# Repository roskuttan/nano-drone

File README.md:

# Nano drone

> [!WARNING]
> **AI-generated and not yet verified in hardware.** This design was produced by Claude (Anthropic's AI) working with
> me. That covers schematic, layout, routing, simulations, fab files and enclosure. No board has been built, powered
> or flown yet. It passes DRC and the simulations in this repo, but simulations are not a substitute for testing.
> Review it yourself before ordering, and use it at your own risk.

> [!NOTE]
> **The controller is not made yet.** This repo has only the drone hardware. Nothing exists yet for the side that
> flies it: no handheld transmitter setup, no phone app, no bridge. The firmware (Rust) for the flight controller and
> the ESCs isn't written either.

A brushless micro quad whose flight board is also its frame: a 36 × 36 mm, 6-layer board carrying an STM32G431
flight controller, four STM32G071 + DRV8311H ESCs, an SX1280 2.4 GHz ELRS radio and an LSM6DSV16X IMU, flying four
0702 motors. Everything is generated by code: schematic, placement, routing, fab outputs and simulations.

<p align="center">
  
</p>

<p align="center"><b>▶ <a href="media/nanodrone_video.mp4?raw=true">Watch the full video in HD</a></b> (40 s, opens in the browser's player)</p>

## PCB (rev C, fully routed: 110/110 nets, DRC 0 errors)

| Top | Bottom |
|---|---|
|  |  |

## Enclosure

| Assembled | Top view |
|---|---|
|  |  |

## Where things are

- [`hw/README.md`](hw/README.md): the generation pipeline, step by step, and how the rev C board was routed.
- [`hw/docs/ARCHITECTURE.md`](hw/docs/ARCHITECTURE.md): system architecture, pin maps, PCB and EMC design.
- [`hw/docs/FIRMWARE_REQUIREMENTS.md`](hw/docs/FIRMWARE_REQUIREMENTS.md): what the (Rust) firmware must do.
- [`hw/sim_post/POST_LAYOUT_REPORT.md`](hw/sim_post/POST_LAYOUT_REPORT.md): post-layout simulations on the routed copper.
- [`hw/output/fab/`](hw/output/fab/): JLCPCB package (Gerbers, BOM, CPL, order notes, STEP).
- [`hw/docs/ENCLOSURE.md`](hw/docs/ENCLOSURE.md): 3D-printed enclosure.

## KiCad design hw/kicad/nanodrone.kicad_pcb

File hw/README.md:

# Nano drone hardware

The flight board is generated by code: schematic, placement, routing, planes, fab outputs and simulations all come
from the Python scripts here. Run them with KiCad 10's bundled Python
(`C:\Users\angel\AppData\Local\Programs\KiCad\10.0\bin\python.exe`).

| Step | Command (from `hw/`) | Output |
|---|---|---|
| 1. Schematic + ERC | `python design/nanodrone_sch.py`, then `kicad-cli sch erc kicad/nanodrone.kicad_sch` | `kicad/*.kicad_sch` |
| 2. Placement + outline | `python design/nanodrone_pcb.py` | `kicad/nanodrone.kicad_pcb` |
| 3. Rules, stackup, critical copper | `python design/nanodrone_route.py prep` | RF feed, driver power, fan-out, escape stubs, planes |
| 4. Routing | `python design/nanodrone_route.py grid` | grid maze router with rip-up and reroute (`tools/gridroute.py`) |
| 4b. Routing, hybrid (alternative to 4) | `python design/nanodrone_route.py route`, then `... repair` | Freerouting for the bulk (prep copper stays locked). `repair` runs DRC and lifts the autorouted copper into the grid router as rip-able routes. It then re-routes incomplete nets and every net in a violation (Freerouting cannot see the `.kicad_dru` EMC rules) with full rules, and prunes dangling copper |
| 5. Finish | `python design/nanodrone_route.py finish` | widen power/phase, pours, stitching/thermal/return vias, DRC |
| 6. Fab package | `python design/nanodrone_fab.py` | `output/fab/`: Gerbers + drill zip, JLC BOM/CPL, order notes, renders, STEP |
| 7. Post-layout simulations | `python sim_post/run_post.py`, then `python sim_post/report.py` | `sim_post/POST_LAYOUT_REPORT.md` |
| Pre-layout simulations | `python sim/run_all.py` | `sim/SIMULATION_REPORT.md` |
| 8. Enclosure | `python tools/board_ref.py <placed or routed board>`, then run the Fusion script `mech/fusion/nanodrone_enclosure` | `output/mech/enclosure/`: STL/STEP for the 3D-printed shells, fit checks, renders (`docs/ENCLOSURE.md`) |

All stages work on `kicad/nanodrone.kicad_pcb`. To work on a copy, set `NANODRONE_PCB` to another board path. For
KiCad's DRC to pick up the design rules, copy `kicad/nanodrone.kicad_pro` and `.kicad_dru` next to that board under
the same base name. `patch_project(pro, dru)` in `design/nanodrone_route.py` writes them for a variant's rules.

The finish stage (step 5) now also removes unused driver escape stubs (`trim_stubs`). It widens only the fixed
motor-current legs; the sense branches stay narrow. Its return-path stitching serves first the signal vias that move
between the L2 and L5 return planes.

### How the rev C board was routed

No single command reproduces the routed board. Steps 1-4 got to 102/110 nets. The rest came from a chain of
seeded repair runs on copies of the board (`NANODRONE_PCB=kicad/nanodrone_<x>.kicad_pcb`). Each run re-routes
only the nets it is told to rip:

1. `legs`: the 12 motor-current legs become fixed copper.
2. `eco_nfault`: removes the four nFAULT pull-ups (rev C, `NANODRONE_NFAULT_PU=0` in the schematic).
3. `repair`, with these settings:
   - 0.10 mm sense branches (`NANODRONE_PHASE_W`), 0.20 mm phase-to-analog spacing;
   - L4 open to digital, rail and analog nets;
   - negotiated congestion. This reached 108/110 (board N20).
4. Local finishing runs on the 0.0125 mm grid (`NANODRONE_GRID_RES`). Each one rips a few named nets
   (`NANODRONE_RIP`), routes them in a set order (`NANODRONE_ORDER`) and keeps the nets it must not touch
   (`NANODRONE_KEEP`). Weighted A* (`NANODRONE_ASTAR_W=1.2`) keeps them fast.
5. `eco_m4col`: moves motor 4's BEMF divider column 0.2 mm east (`M4_COL_X` in `design/nanodrone_pcb.py`), so
   ESC4's SWD pins get via sites.
6. Local finishing with phase sense branches allowed on L4. In order:
   - the rest of the SWD clock;
   - motor 1's phase A/B sense lines, which had blocked ESC1's SWCLK pin;
   - motor 4 phase A, after moving ESC4_SWDIO off its via site;
   - M4_DSHOT and M4_INLA, whose vias the column shift had come too close to.

   The result is `kicad/attempts/nanodrone_r1.kicad_pcb`: 110/110 nets. All intermediate boards are kept in
   `kicad/attempts/`.
7. The finish stage then found a floating B-pour island under U24. It held J2's antenna GND pad and the GND pads of
   motor 4's BEMF B/C dividers, so those dividers had no ground. No via fitted inside the island.
   - A GND via went in at (-3.76, -6.24), the one spot inside the island blocked only by a single net (M4_nSLEEP).
   - M4_nSLEEP was re-routed off L4. Analog and control nets re-routed through L4 there could split the VBAT plane
     feeding motor 4's driver.
   - Result: `kicad/nanodrone_z2.kicad_pcb`. DRC shows 0 violations and 0 unconnected items.

The finish stage now runs `stitch_islands`. It gives any GND pour island without a via its own via, or reports it.

Router lessons from that work (`tools/gridroute.py`):
- **Own copper:** counts as free only after eroding it by half a track plus the grid margin. Otherwise connections
  creep into a neighbour's clearance; this caused a real short.
- **Hard cells:** these and the board edge keep half a track. No-net pads keep 0.15 mm plus their mask opening.
- **Grid size:** 0.0125 mm wins about 10-20 % of channel capacity over 0.025 mm.
- **Multi-pin nets:** retry from another pin when the first one is boxed in, and defer clusters that fail.
- **KiCad rules:** the last matching custom rule wins, so the specific phase-to-analog rule comes last in
  `.kicad_dru`. `kicad-cli` needs `--all-track-errors` to report every error on a track.

Documents:
- `docs/ARCHITECTURE.md`: system architecture, pin maps, PCB, EMC and firmware notes.
- `docs/FIRMWARE_REQUIREMENTS.md`: what the Rust firmware must do because of the hardware.
- `docs/COST_ESTIMATE.md`: batch and per-drone cost.
- `docs/ENCLOSURE.md`: 3D-printed enclosure: design, mass and TWR, fit checks, printing and assembly.

Tools:
- `tools/kisch.py`: schematic-as-code.
- `tools/kifp.py`: custom footprints.
- `tools/kipcb.py`: placement helpers.
- `tools/gridroute.py`: router.
- `tools/render.py` and `tools/zoom.py`: PNG views.
- `tools/board_ref.py`: mechanical reference of the board (outline, holes, part boxes, motors) for the enclosure.
- `mech/enclosure_calcs.py`: hand calculations for the enclosure (duct sections, ring mode, struts, mass/TWR).

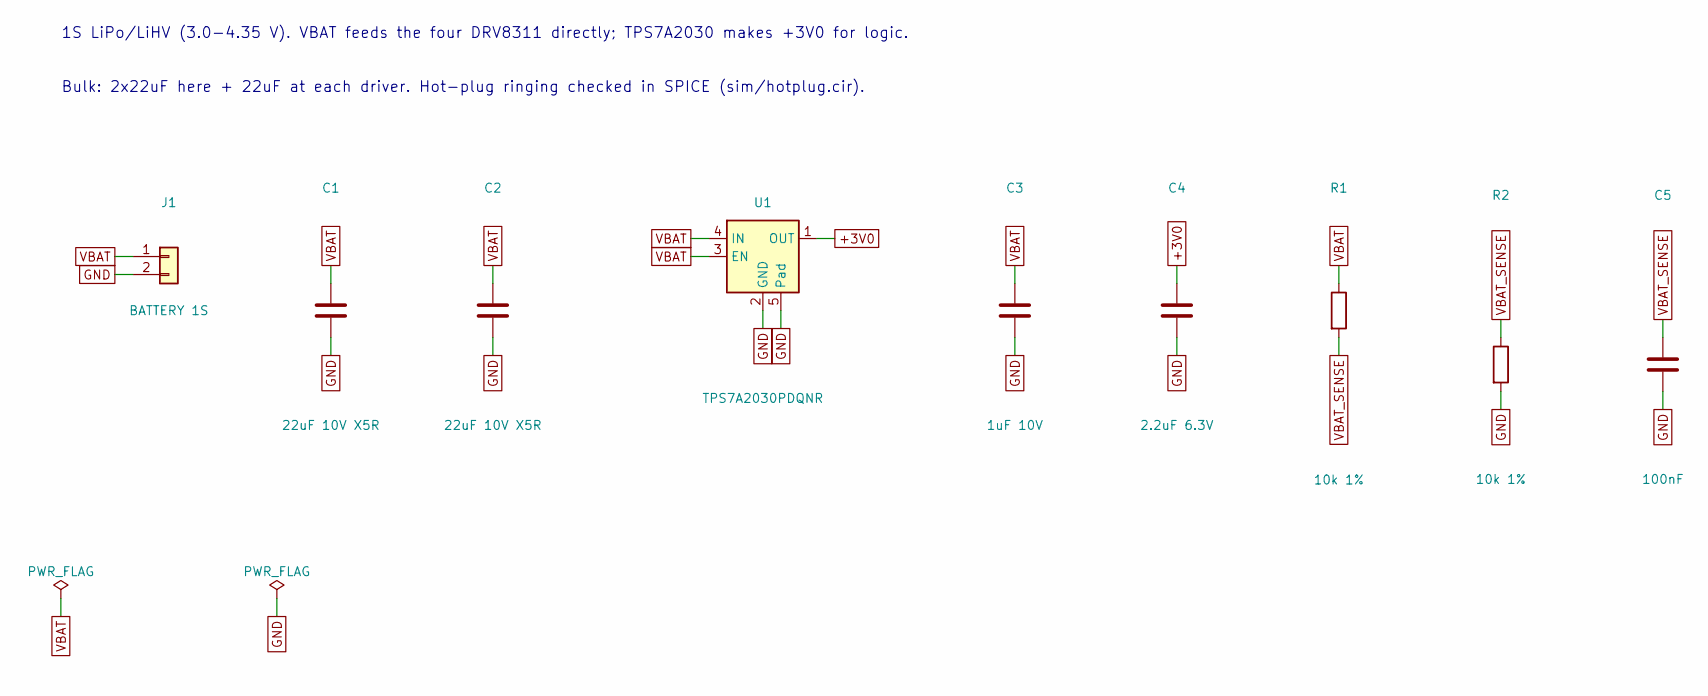
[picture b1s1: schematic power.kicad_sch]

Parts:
C1, C2: 22uF 10V X5R; C_0603_1608Metric
C3: 1uF 10V; C_0402_1005Metric
C4: 2.2uF 6.3V; C_0402_1005Metric
C5: 100nF; C_0201_0603Metric
J1: BATTERY 1S; BatteryPads_PTH
R1, R2: 10k 1%; R_0201_0603Metric
U1: TPS7A2030PDQNR; Texas_X2SON-4_1x1mm_P0.65mm; MPN TPS7A2030PDQNR

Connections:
+3V0: C4.1, U1.1 (OUT); also elsewhere on the board
GND: C1.2, C2.2, C3.2, C4.2, C5.2, J1.2, R2.2, U1.2 (GND), U1.5 (Pad); also elsewhere on the board
VBAT: C1.1, C2.1, C3.1, J1.1, R1.1, U1.3 (EN), U1.4 (IN); also elsewhere on the board
VBAT_SENSE: C5.1, R1.2, R2.1; also elsewhere on the board

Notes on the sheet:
1S LiPo/LiHV (3.0-4.35 V). VBAT feeds the four DRV8311 directly; TPS7A2030 makes +3V0 for logic.
Bulk: 2x22uF here + 22uF at each driver. Hot-plug ringing checked in SPICE (sim/hotplug.cir).

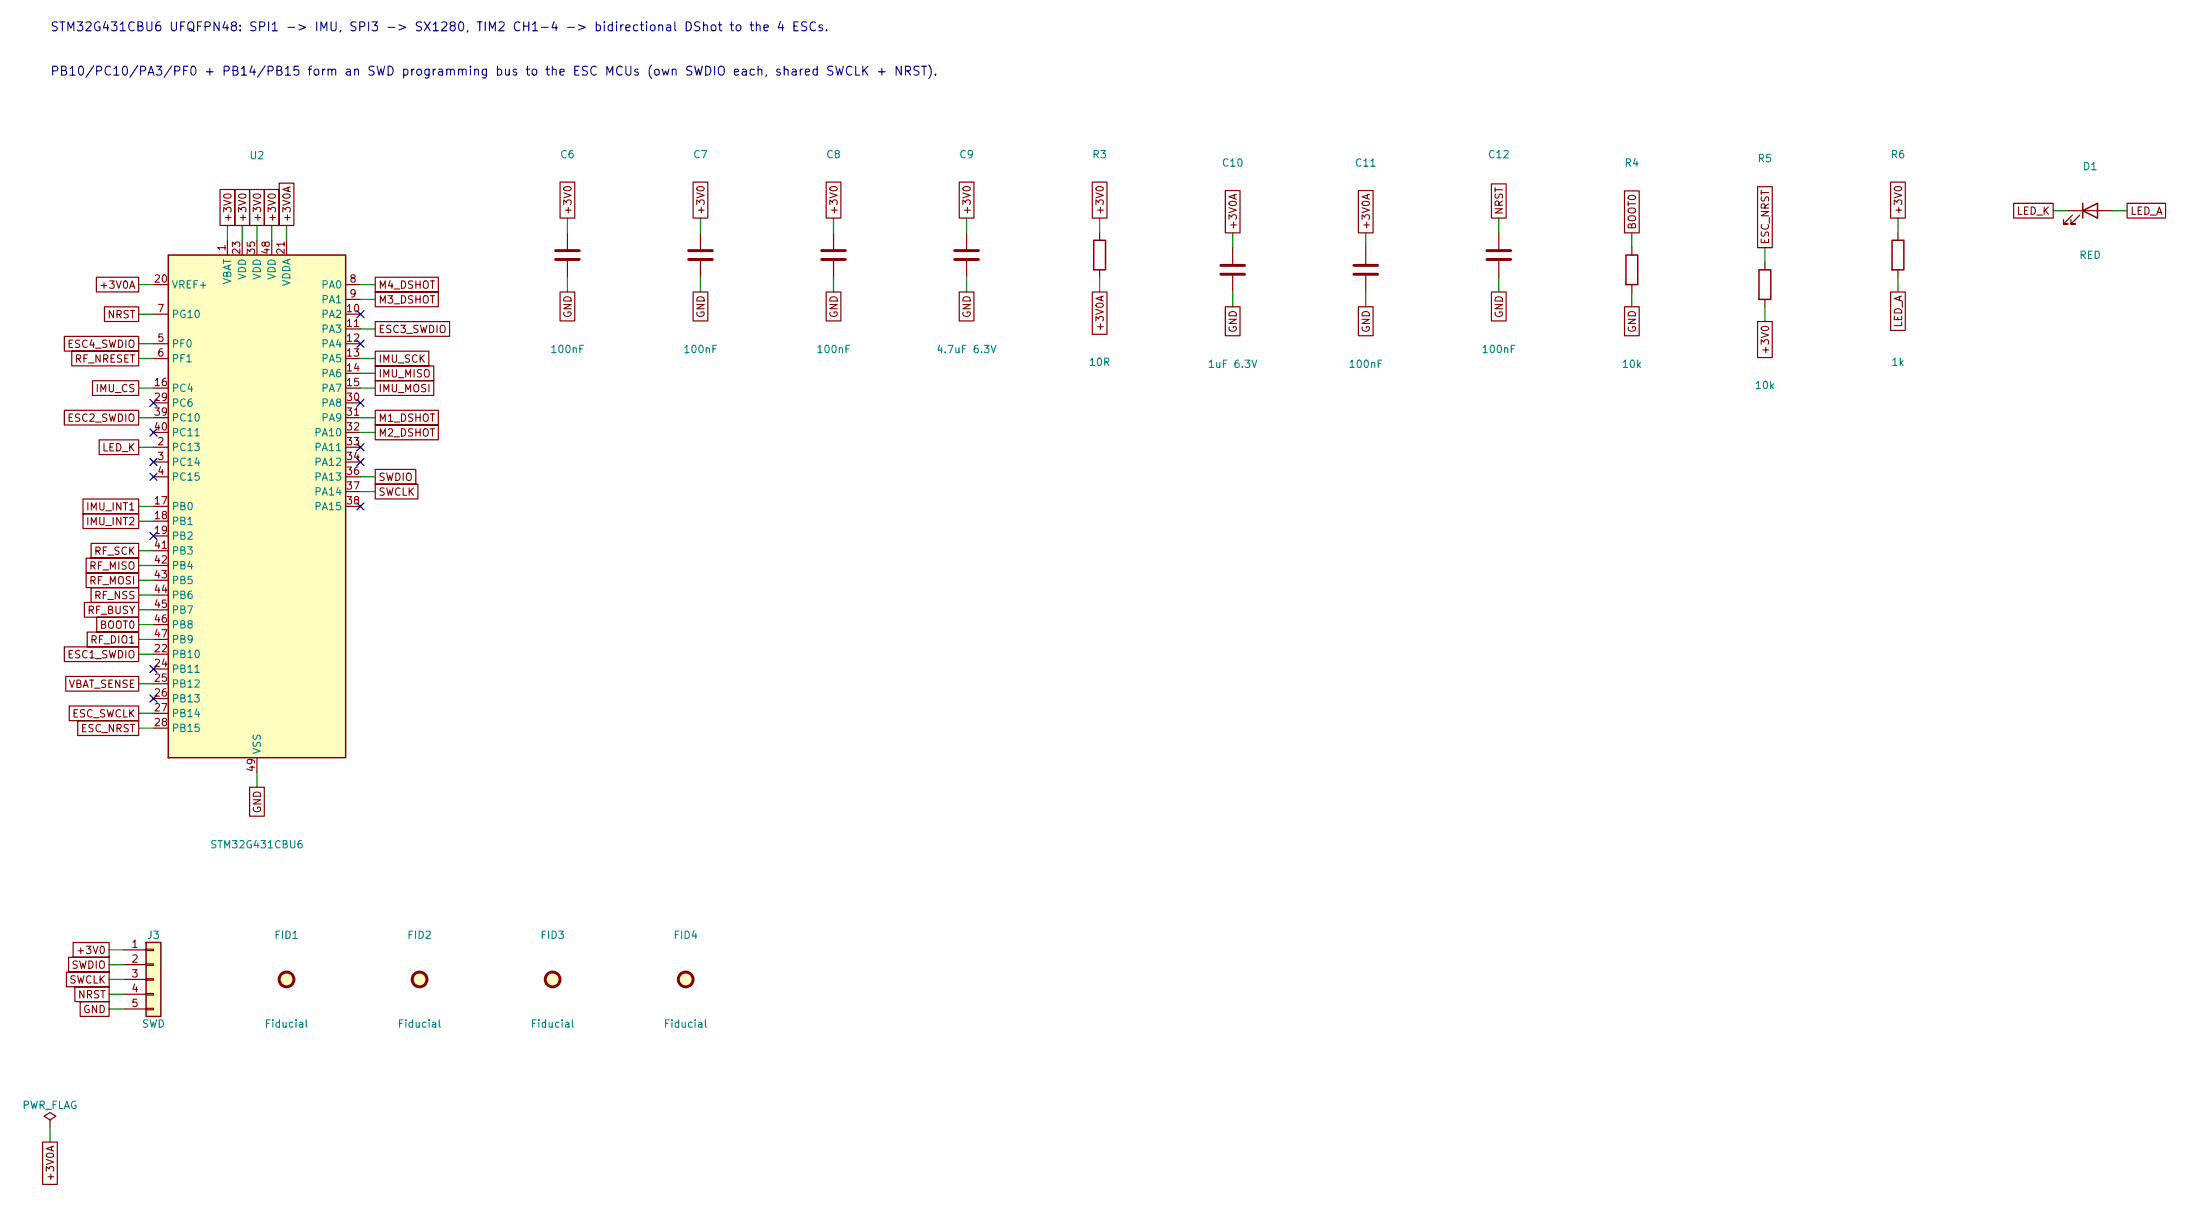
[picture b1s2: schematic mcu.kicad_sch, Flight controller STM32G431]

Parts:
C6, C7, C8, C11, C12: 100nF; C_0201_0603Metric
C9: 4.7uF 6.3V; C_0402_1005Metric
C10: 1uF 6.3V; C_0201_0603Metric
D1: RED; LED_0402_1005Metric
FID1, FID2, FID3, FID4: Fiducial; Fiducial_0.6mm_Mask1.2mm
J3: SWD; SWD_Pads_1x05_P1.27mm
R3: 10R; R_0201_0603Metric
R4, R5: 10k; R_0201_0603Metric
R6: 1k; R_0201_0603Metric
U2: STM32G431CBU6; QFN-48-1EP_7x7mm_P0.5mm_EP5.6x5.6mm; MPN STM32G431CBU6; LCSC C529356

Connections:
+3V0: C6.1, C7.1, C8.1, C9.1, J3.1, R3.1, R5.2, R6.1, U2.1 (VBAT), U2.23 (VDD), U2.35 (VDD), U2.48 (VDD); also elsewhere on the board
+3V0A: C10.1, C11.1, R3.2, U2.20 (VREF+), U2.21 (VDDA)
BOOT0: R4.1, U2.46 (PB8)
ESC1_SWDIO: U2.22 (PB10); also elsewhere on the board
ESC2_SWDIO: U2.39 (PC10); also elsewhere on the board
ESC3_SWDIO: U2.11 (PA3); also elsewhere on the board
ESC4_SWDIO: U2.5 (PF0); also elsewhere on the board
ESC_NRST: R5.1, U2.28 (PB15); also elsewhere on the board
ESC_SWCLK: U2.27 (PB14); also elsewhere on the board
GND: C6.2, C7.2, C8.2, C9.2, C10.2, C11.2, C12.2, J3.5, R4.2, U2.49 (VSS); also elsewhere on the board
IMU_CS: U2.16 (PC4); also elsewhere on the board
IMU_INT1: U2.17 (PB0); also elsewhere on the board
IMU_INT2: U2.18 (PB1); also elsewhere on the board
IMU_MISO: U2.14 (PA6); also elsewhere on the board
IMU_MOSI: U2.15 (PA7); also elsewhere on the board
IMU_SCK: U2.13 (PA5); also elsewhere on the board
LED_A: D1.2 (A), R6.2
LED_K: D1.1 (K), U2.2 (PC13)
M1_DSHOT: U2.31 (PA9); also elsewhere on the board
M2_DSHOT: U2.32 (PA10); also elsewhere on the board
M3_DSHOT: U2.9 (PA1); also elsewhere on the board
M4_DSHOT: U2.8 (PA0); also elsewhere on the board
NRST: C12.1, J3.4, U2.7 (PG10)
RF_BUSY: U2.45 (PB7); also elsewhere on the board
RF_DIO1: U2.47 (PB9); also elsewhere on the board
RF_MISO: U2.42 (PB4); also elsewhere on the board
RF_MOSI: U2.43 (PB5); also elsewhere on the board
RF_NRESET: U2.6 (PF1); also elsewhere on the board
RF_NSS: U2.44 (PB6); also elsewhere on the board
RF_SCK: U2.41 (PB3); also elsewhere on the board
SWCLK: J3.3, U2.37 (PA14)
SWDIO: J3.2, U2.36 (PA13)
VBAT_SENSE: U2.25 (PB12); also elsewhere on the board

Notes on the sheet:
STM32G431CBU6 UFQFPN48: SPI1 -> IMU, SPI3 -> SX1280, TIM2 CH1-4 -> bidirectional DShot to the 4 ESCs.
PB10/PC10/PA3/PF0 + PB14/PB15 form an SWD programming bus to the ESC MCUs (own SWDIO each, shared SWCLK + NRST).

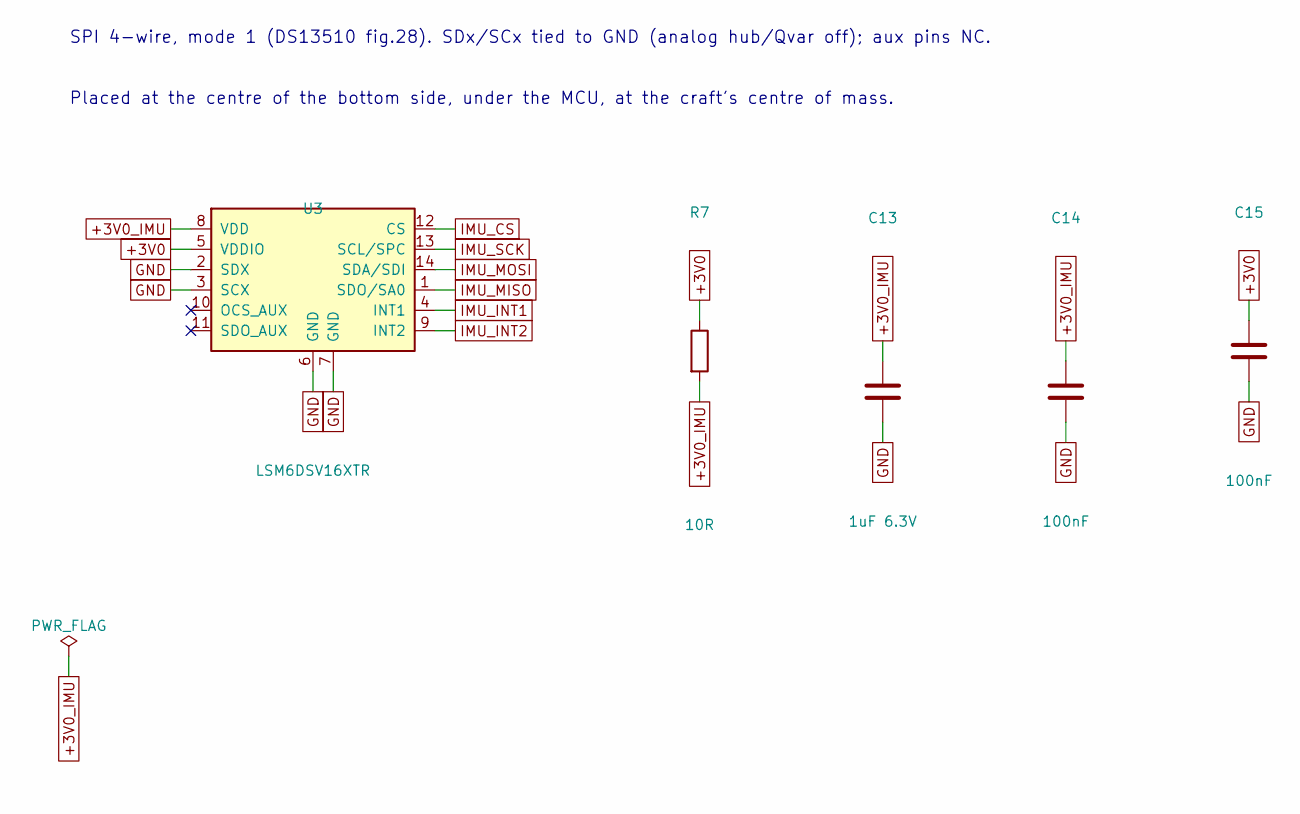
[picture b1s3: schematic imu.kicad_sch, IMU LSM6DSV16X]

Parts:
C13: 1uF 6.3V; C_0201_0603Metric
C14, C15: 100nF; C_0201_0603Metric
R7: 10R; R_0201_0603Metric
U3: LSM6DSV16XTR; LGA-14_3x2.5mm_P0.5mm_LayoutBorder3x4y; MPN LSM6DSV16XTR; LCSC C5267406

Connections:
+3V0: C15.1, R7.1, U3.5 (VDDIO); also elsewhere on the board
+3V0_IMU: C13.1, C14.1, R7.2, U3.8 (VDD)
GND: C13.2, C14.2, C15.2, U3.2 (SDX), U3.3 (SCX), U3.6 (GND), U3.7 (GND); also elsewhere on the board
IMU_CS: U3.12 (CS); also elsewhere on the board
IMU_INT1: U3.4 (INT1); also elsewhere on the board
IMU_INT2: U3.9 (INT2); also elsewhere on the board
IMU_MISO: U3.1 (SDO/SA0); also elsewhere on the board
IMU_MOSI: U3.14 (SDA/SDI); also elsewhere on the board
IMU_SCK: U3.13 (SCL/SPC); also elsewhere on the board

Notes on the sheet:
SPI 4-wire, mode 1 (DS13510 fig.28). SDx/SCx tied to GND (analog hub/Qvar off); aux pins NC.
Placed at the centre of the bottom side, under the MCU, at the craft's centre of mass.

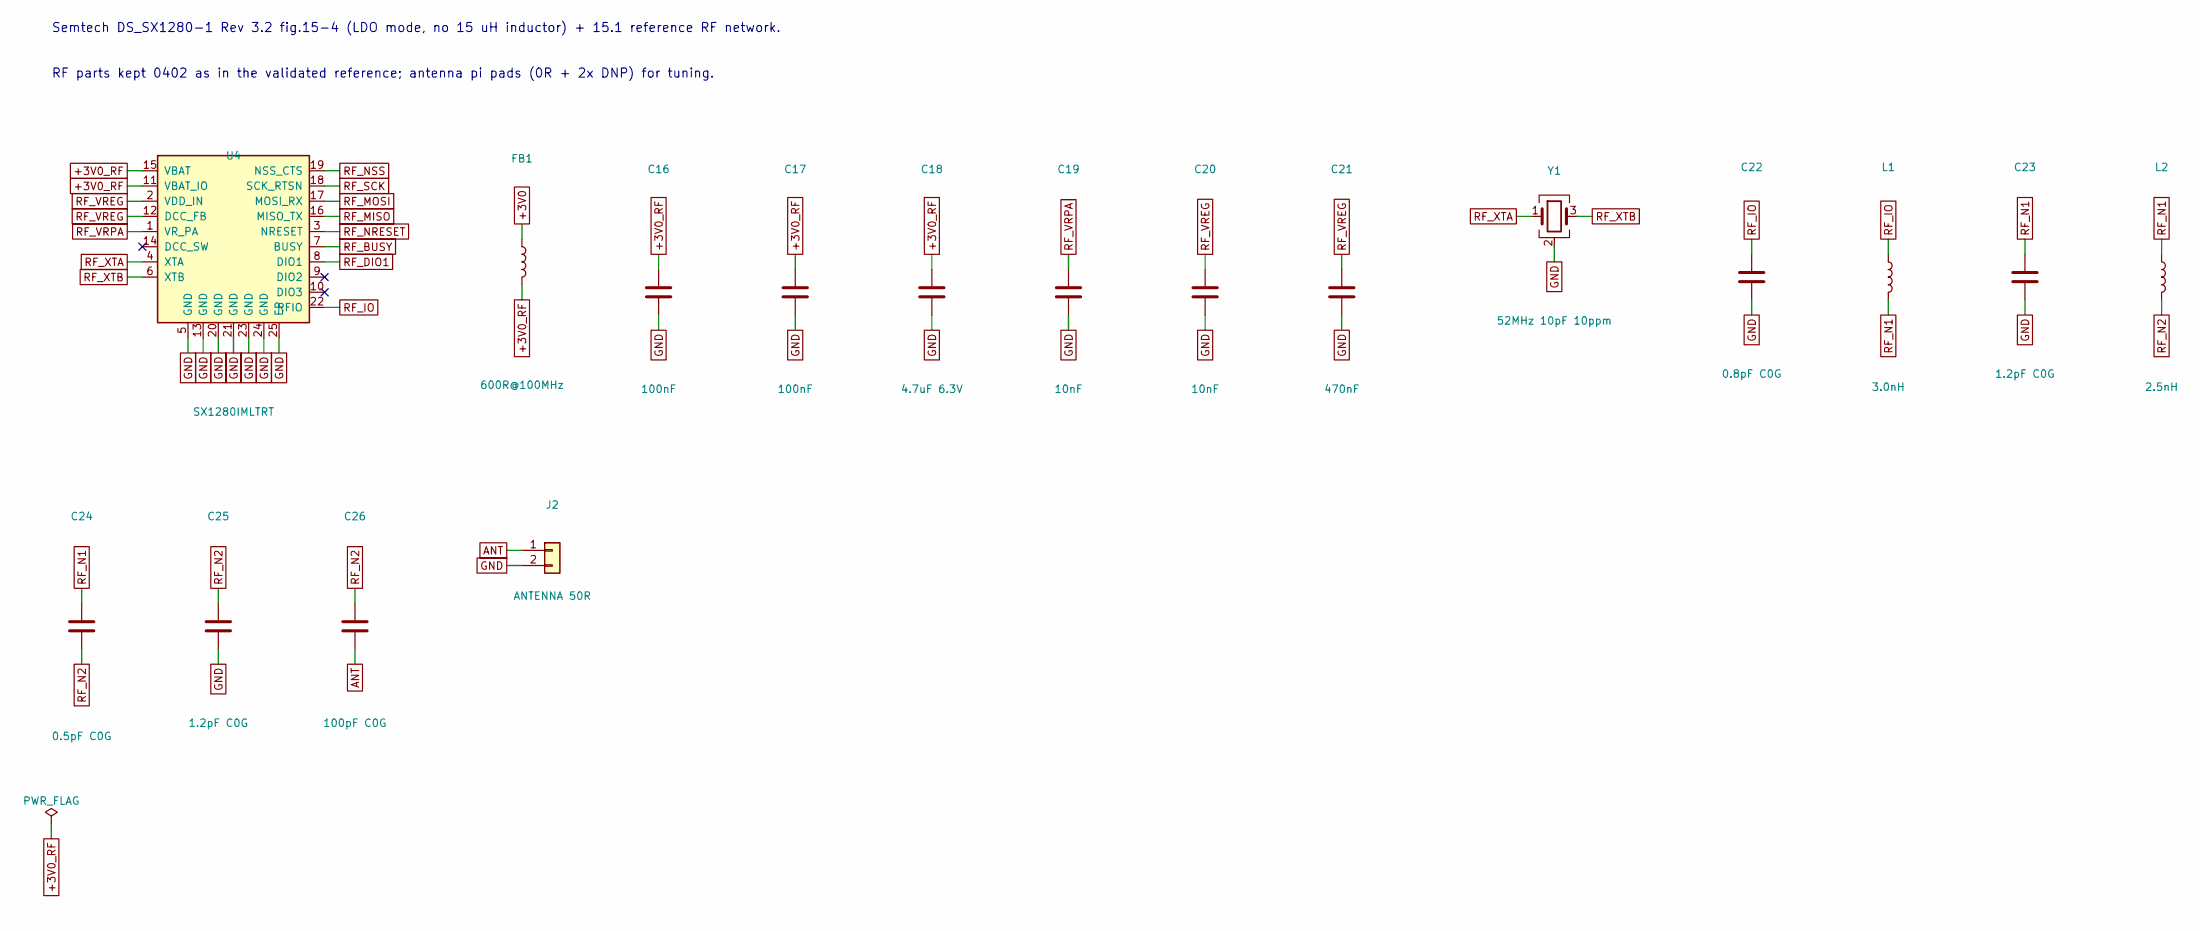
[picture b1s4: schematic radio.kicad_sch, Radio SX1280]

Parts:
C16, C17: 100nF; C_0402_1005Metric
C18: 4.7uF 6.3V; C_0402_1005Metric
C19, C20: 10nF; C_0402_1005Metric
C21: 470nF; C_0402_1005Metric
C22: 0.8pF C0G; C_0402_1005Metric
C23, C25: 1.2pF C0G; C_0402_1005Metric
C24: 0.5pF C0G; C_0402_1005Metric
C26: 100pF C0G; C_0402_1005Metric
FB1: 600R@100MHz; L_0402_1005Metric
J2: ANTENNA 50R; AntennaPads_SMD
L1: 3.0nH; L_0402_1005Metric
L2: 2.5nH; L_0402_1005Metric
U4: SX1280IMLTRT; QFN-24-1EP_4x4mm_P0.5mm_EP2.7x2.7mm_ThermalVias; MPN SX1280IMLTRT; LCSC C125969
Y1: 52MHz 10pF 10ppm; Crystal_SMD_2016-4Pin_2.0x1.6mm

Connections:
+3V0: FB1.1; also elsewhere on the board
+3V0_RF: C16.1, C17.1, C18.1, FB1.2, U4.11 (VBAT_IO), U4.15 (VBAT)
ANT: C26.2, J2.1
GND: C16.2, C17.2, C18.2, C19.2, C20.2, C21.2, C22.2, C23.2, C25.2, J2.2, U4.5 (GND), U4.13 (GND), U4.20 (GND), U4.21 (GND), U4.23 (GND), U4.24 (GND), U4.25 (EP), Y1.2 (G), Y1.4 (G); also elsewhere on the board
RF_BUSY: U4.7 (BUSY); also elsewhere on the board
RF_DIO1: U4.8 (DIO1); also elsewhere on the board
RF_IO: C22.1, L1.1, U4.22 (RFIO)
RF_MISO: U4.16 (MISO_TX); also elsewhere on the board
RF_MOSI: U4.17 (MOSI_RX); also elsewhere on the board
RF_N1: C23.1, C24.1, L1.2, L2.1
RF_N2: C24.2, C25.1, C26.1, L2.2
RF_NRESET: U4.3 (NRESET); also elsewhere on the board
RF_NSS: U4.19 (NSS_CTS); also elsewhere on the board
RF_SCK: U4.18 (SCK_RTSN); also elsewhere on the board
RF_VREG: C20.1, C21.1, U4.2 (VDD_IN), U4.12 (DCC_FB)
RF_VRPA: C19.1, U4.1 (VR_PA)
RF_XTA: U4.4 (XTA), Y1.1
RF_XTB: U4.6 (XTB), Y1.3

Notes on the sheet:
Semtech DS_SX1280-1 Rev 3.2 fig.15-4 (LDO mode, no 15 uH inductor) + 15.1 reference RF network.
RF parts kept 0402 as in the validated reference; antenna pi pads (0R + 2x DNP) for tuning.

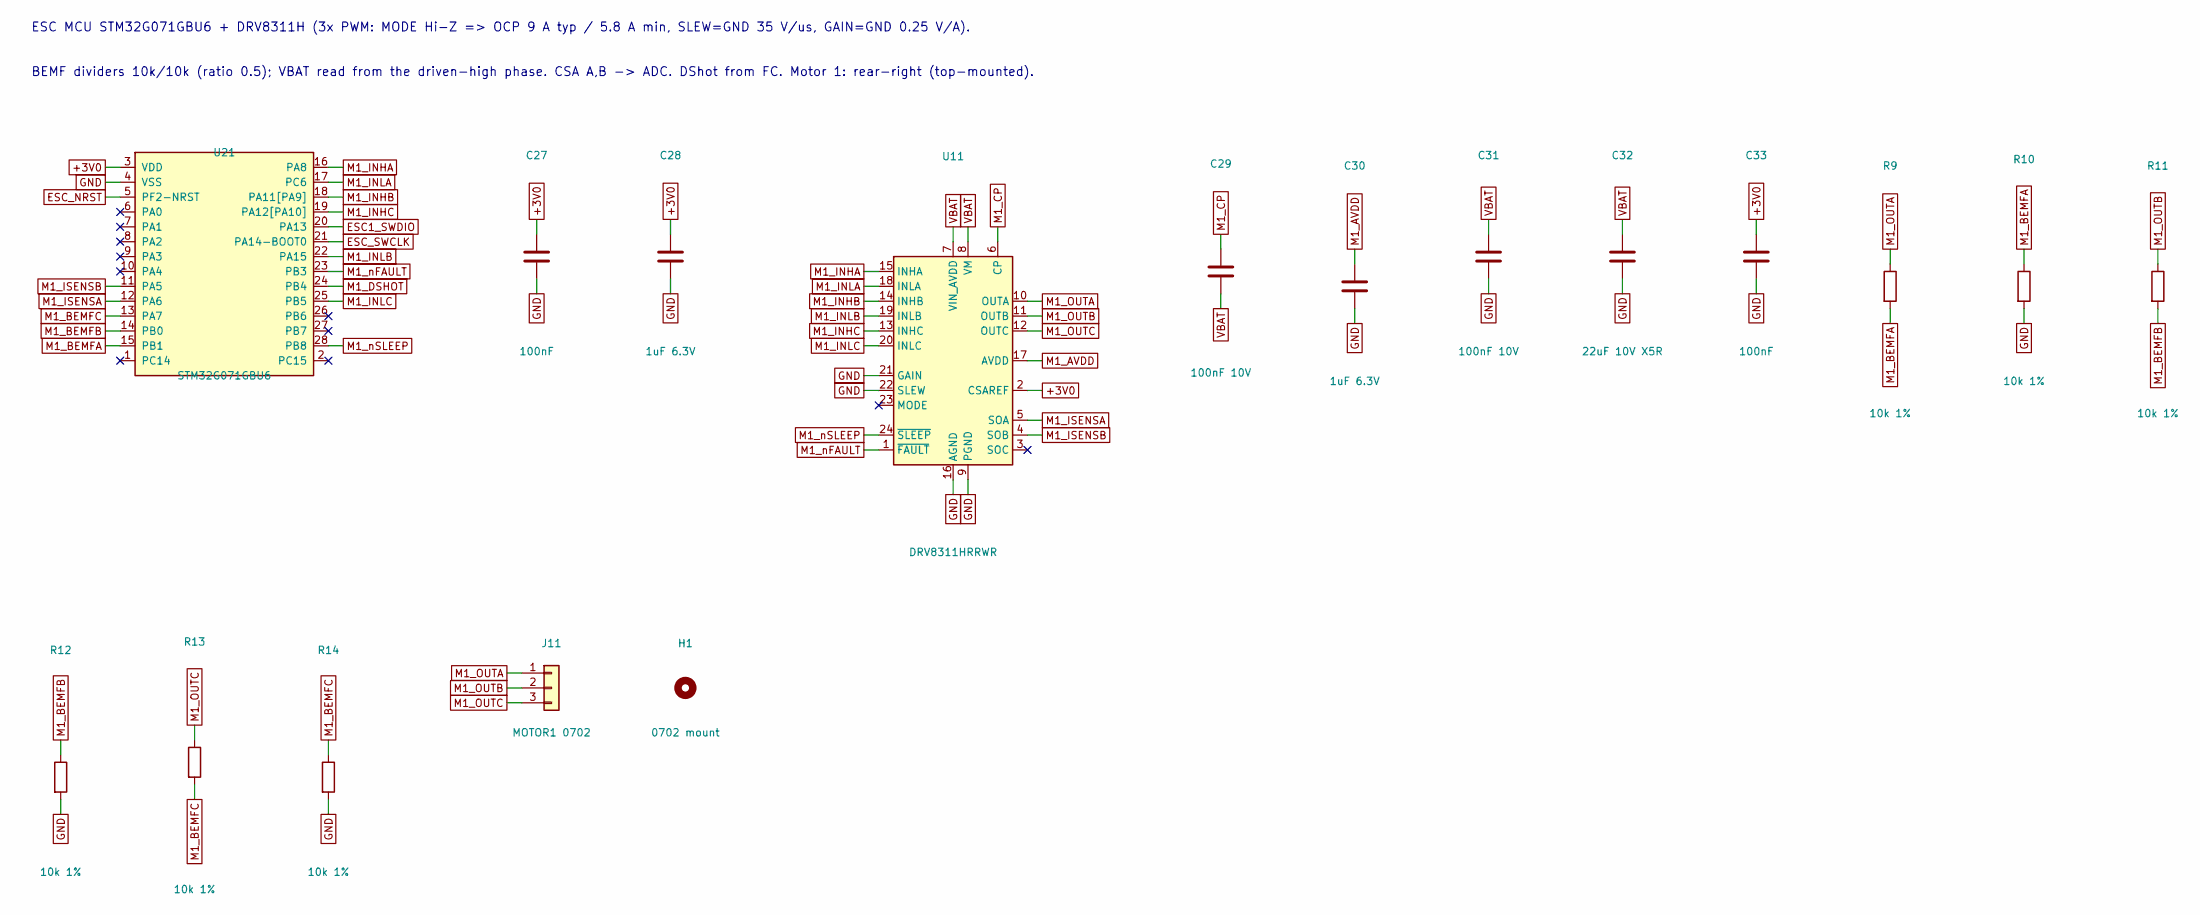
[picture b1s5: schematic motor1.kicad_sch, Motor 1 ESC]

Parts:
C27, C33: 100nF; C_0201_0603Metric
C28, C30: 1uF 6.3V; C_0201_0603Metric
C29, C31: 100nF 10V; C_0201_0603Metric
C32: 22uF 10V X5R; C_0603_1608Metric
H1: 0702 mount; Motor_0702_Mount
J11: MOTOR1 0702; MotorPads_3x_PTH
R9, R10, R11, R12, R13, R14: 10k 1%; R_0201_0603Metric
U11: DRV8311HRRWR; Texas_RRW0024A_WQFN-24-1EP_3x3mm_P0.4mm_EP1.9x1.9mm_Thermal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; MPN DRV8311HRRWR; LCSC C5218862
U21: STM32G071GBU6; QFN-28_4x4mm_P0.5mm; MPN STM32G071GBU6; LCSC C529347

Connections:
+3V0: C27.1, C28.1, C33.1, U11.2 (CSAREF), U21.3 (VDD); also elsewhere on the board
ESC1_SWDIO: U21.20 (PA13); also elsewhere on the board
ESC_NRST: U21.5 (PF2-NRST); also elsewhere on the board
ESC_SWCLK: U21.21 (PA14-BOOT0); also elsewhere on the board
GND: C27.2, C28.2, C30.2, C31.2, C32.2, C33.2, R10.2, R12.2, R14.2, U11.9 (PGND), U11.16 (AGND), U11.21 (GAIN), U11.22 (SLEW), U11.25 (PGND), U21.4 (VSS); also elsewhere on the board
M1_AVDD: C30.1, U11.17 (AVDD)
M1_BEMFA: R9.2, R10.1, U21.15 (PB1)
M1_BEMFB: R11.2, R12.1, U21.14 (PB0)
M1_BEMFC: R13.2, R14.1, U21.13 (PA7)
M1_CP: C29.1, U11.6 (CP)
M1_DSHOT: U21.24 (PB4); also elsewhere on the board
M1_INHA: U11.15 (INHA), U21.16 (PA8)
M1_INHB: U11.14 (INHB), U21.18 (PA11[PA9])
M1_INHC: U11.13 (INHC), U21.19 (PA12[PA10])
M1_INLA: U11.18 (INLA), U21.17 (PC6)
M1_INLB: U11.19 (INLB), U21.22 (PA15)
M1_INLC: U11.20 (INLC), U21.25 (PB5)
M1_ISENSA: U11.5 (SOA), U21.12 (PA6)
M1_ISENSB: U11.4 (SOB), U21.11 (PA5)
M1_OUTA: J11.1, R9.1, U11.10 (OUTA)
M1_OUTB: J11.2, R11.1, U11.11 (OUTB)
M1_OUTC: J11.3, R13.1, U11.12 (OUTC)
M1_nFAULT: U11.1 (~FAULT), U21.23 (PB3)
M1_nSLEEP: U11.24 (~SLEEP), U21.28 (PB8)
VBAT: C29.2, C31.1, C32.1, U11.7 (VIN_AVDD), U11.8 (VM); also elsewhere on the board

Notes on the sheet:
ESC MCU STM32G071GBU6 + DRV8311H (3x PWM: MODE Hi-Z => OCP 9 A typ / 5.8 A min, SLEW=GND 35 V/us, GAIN=GND 0.25 V/A).
BEMF dividers 10k/10k (ratio 0.5); VBAT read from the driven-high phase. CSA A,B -> ADC. DShot from FC. Motor 1: rear-right (top-mounted).

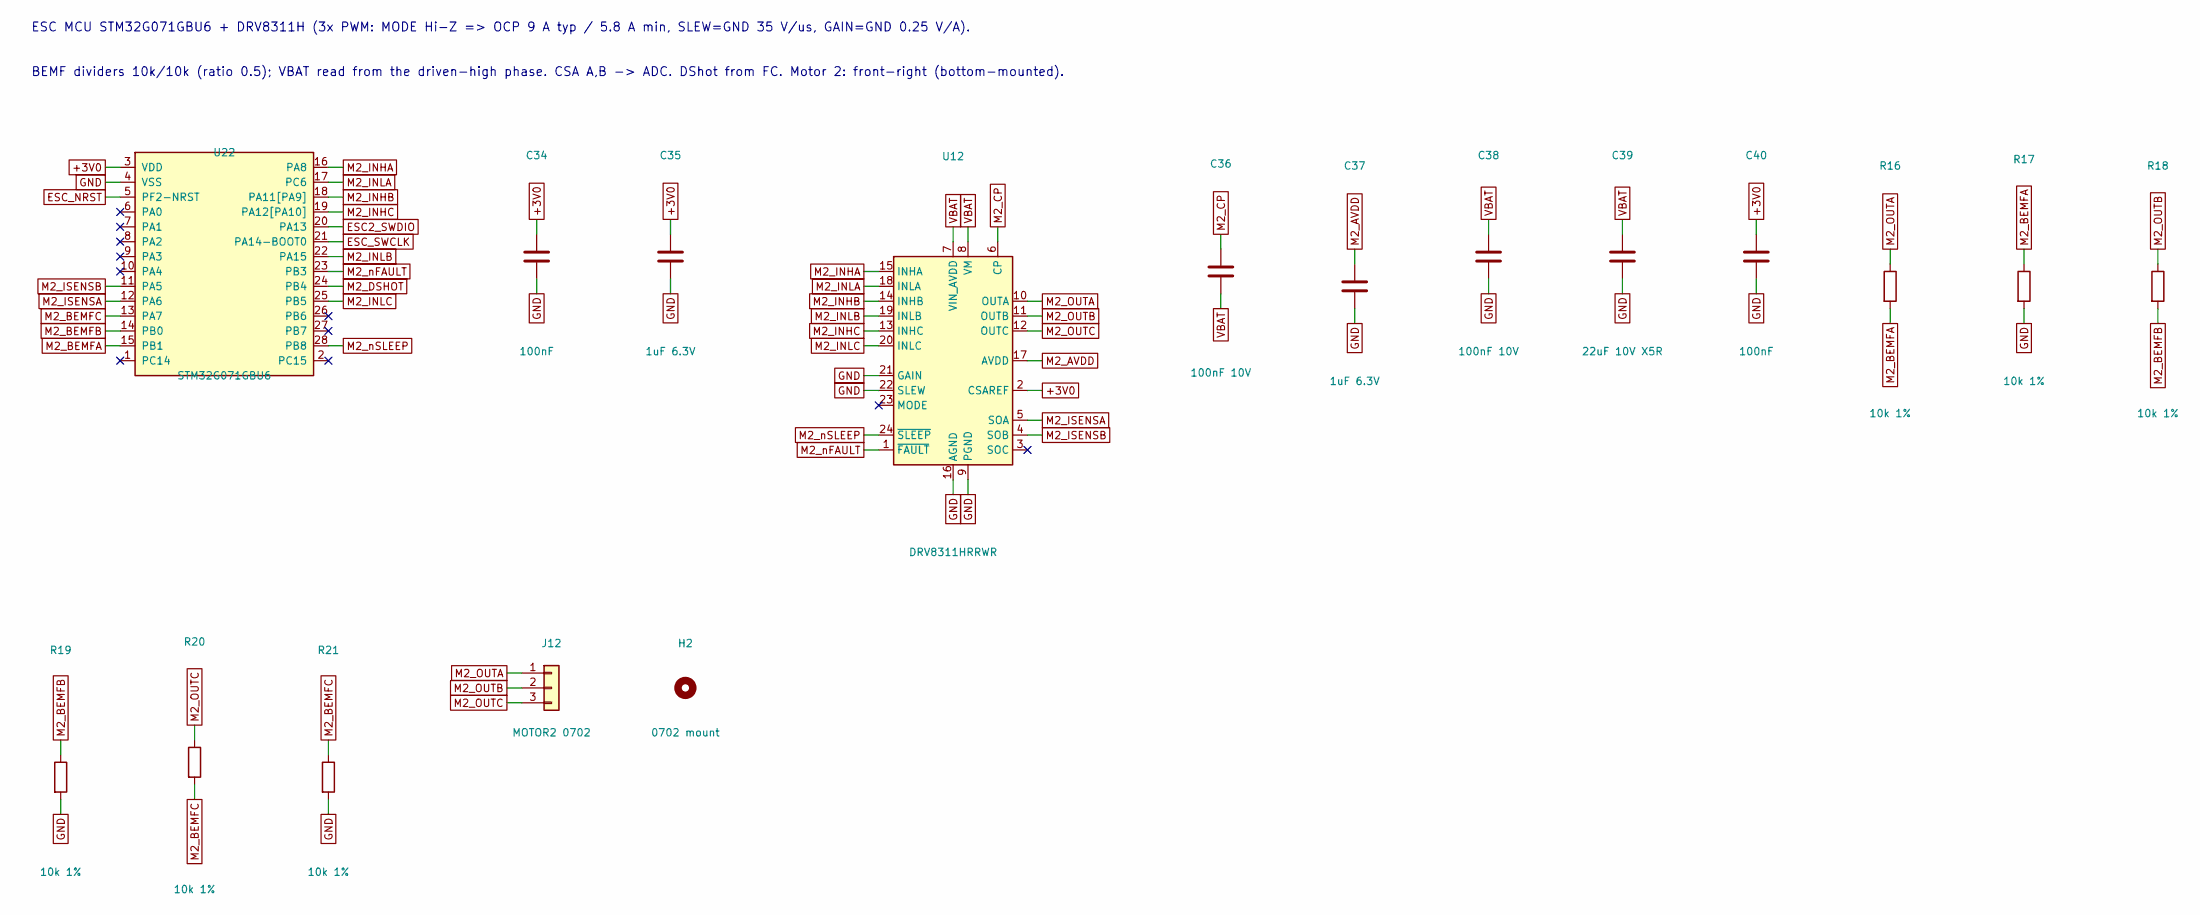
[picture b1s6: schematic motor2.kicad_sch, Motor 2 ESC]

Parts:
C34, C40: 100nF; C_0201_0603Metric
C35, C37: 1uF 6.3V; C_0201_0603Metric
C36, C38: 100nF 10V; C_0201_0603Metric
C39: 22uF 10V X5R; C_0603_1608Metric
H2: 0702 mount; Motor_0702_Mount
J12: MOTOR2 0702; MotorPads_3x_PTH
R16, R17, R18, R19, R20, R21: 10k 1%; R_0201_0603Metric
U12: DRV8311HRRWR; Texas_RRW0024A_WQFN-24-1EP_3x3mm_P0.4mm_EP1.9x1.9mm_Thermal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; MPN DRV8311HRRWR; LCSC C5218862
U22: STM32G071GBU6; QFN-28_4x4mm_P0.5mm; MPN STM32G071GBU6; LCSC C529347

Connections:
+3V0: C34.1, C35.1, C40.1, U12.2 (CSAREF), U22.3 (VDD); also elsewhere on the board
ESC2_SWDIO: U22.20 (PA13); also elsewhere on the board
ESC_NRST: U22.5 (PF2-NRST); also elsewhere on the board
ESC_SWCLK: U22.21 (PA14-BOOT0); also elsewhere on the board
GND: C34.2, C35.2, C37.2, C38.2, C39.2, C40.2, R17.2, R19.2, R21.2, U12.9 (PGND), U12.16 (AGND), U12.21 (GAIN), U12.22 (SLEW), U12.25 (PGND), U22.4 (VSS); also elsewhere on the board
M2_AVDD: C37.1, U12.17 (AVDD)
M2_BEMFA: R16.2, R17.1, U22.15 (PB1)
M2_BEMFB: R18.2, R19.1, U22.14 (PB0)
M2_BEMFC: R20.2, R21.1, U22.13 (PA7)
M2_CP: C36.1, U12.6 (CP)
M2_DSHOT: U22.24 (PB4); also elsewhere on the board
M2_INHA: U12.15 (INHA), U22.16 (PA8)
M2_INHB: U12.14 (INHB), U22.18 (PA11[PA9])
M2_INHC: U12.13 (INHC), U22.19 (PA12[PA10])
M2_INLA: U12.18 (INLA), U22.17 (PC6)
M2_INLB: U12.19 (INLB), U22.22 (PA15)
M2_INLC: U12.20 (INLC), U22.25 (PB5)
M2_ISENSA: U12.5 (SOA), U22.12 (PA6)
M2_ISENSB: U12.4 (SOB), U22.11 (PA5)
M2_OUTA: J12.1, R16.1, U12.10 (OUTA)
M2_OUTB: J12.2, R18.1, U12.11 (OUTB)
M2_OUTC: J12.3, R20.1, U12.12 (OUTC)
M2_nFAULT: U12.1 (~FAULT), U22.23 (PB3)
M2_nSLEEP: U12.24 (~SLEEP), U22.28 (PB8)
VBAT: C36.2, C38.1, C39.1, U12.7 (VIN_AVDD), U12.8 (VM); also elsewhere on the board

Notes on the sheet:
ESC MCU STM32G071GBU6 + DRV8311H (3x PWM: MODE Hi-Z => OCP 9 A typ / 5.8 A min, SLEW=GND 35 V/us, GAIN=GND 0.25 V/A).
BEMF dividers 10k/10k (ratio 0.5); VBAT read from the driven-high phase. CSA A,B -> ADC. DShot from FC. Motor 2: front-right (bottom-mounted).

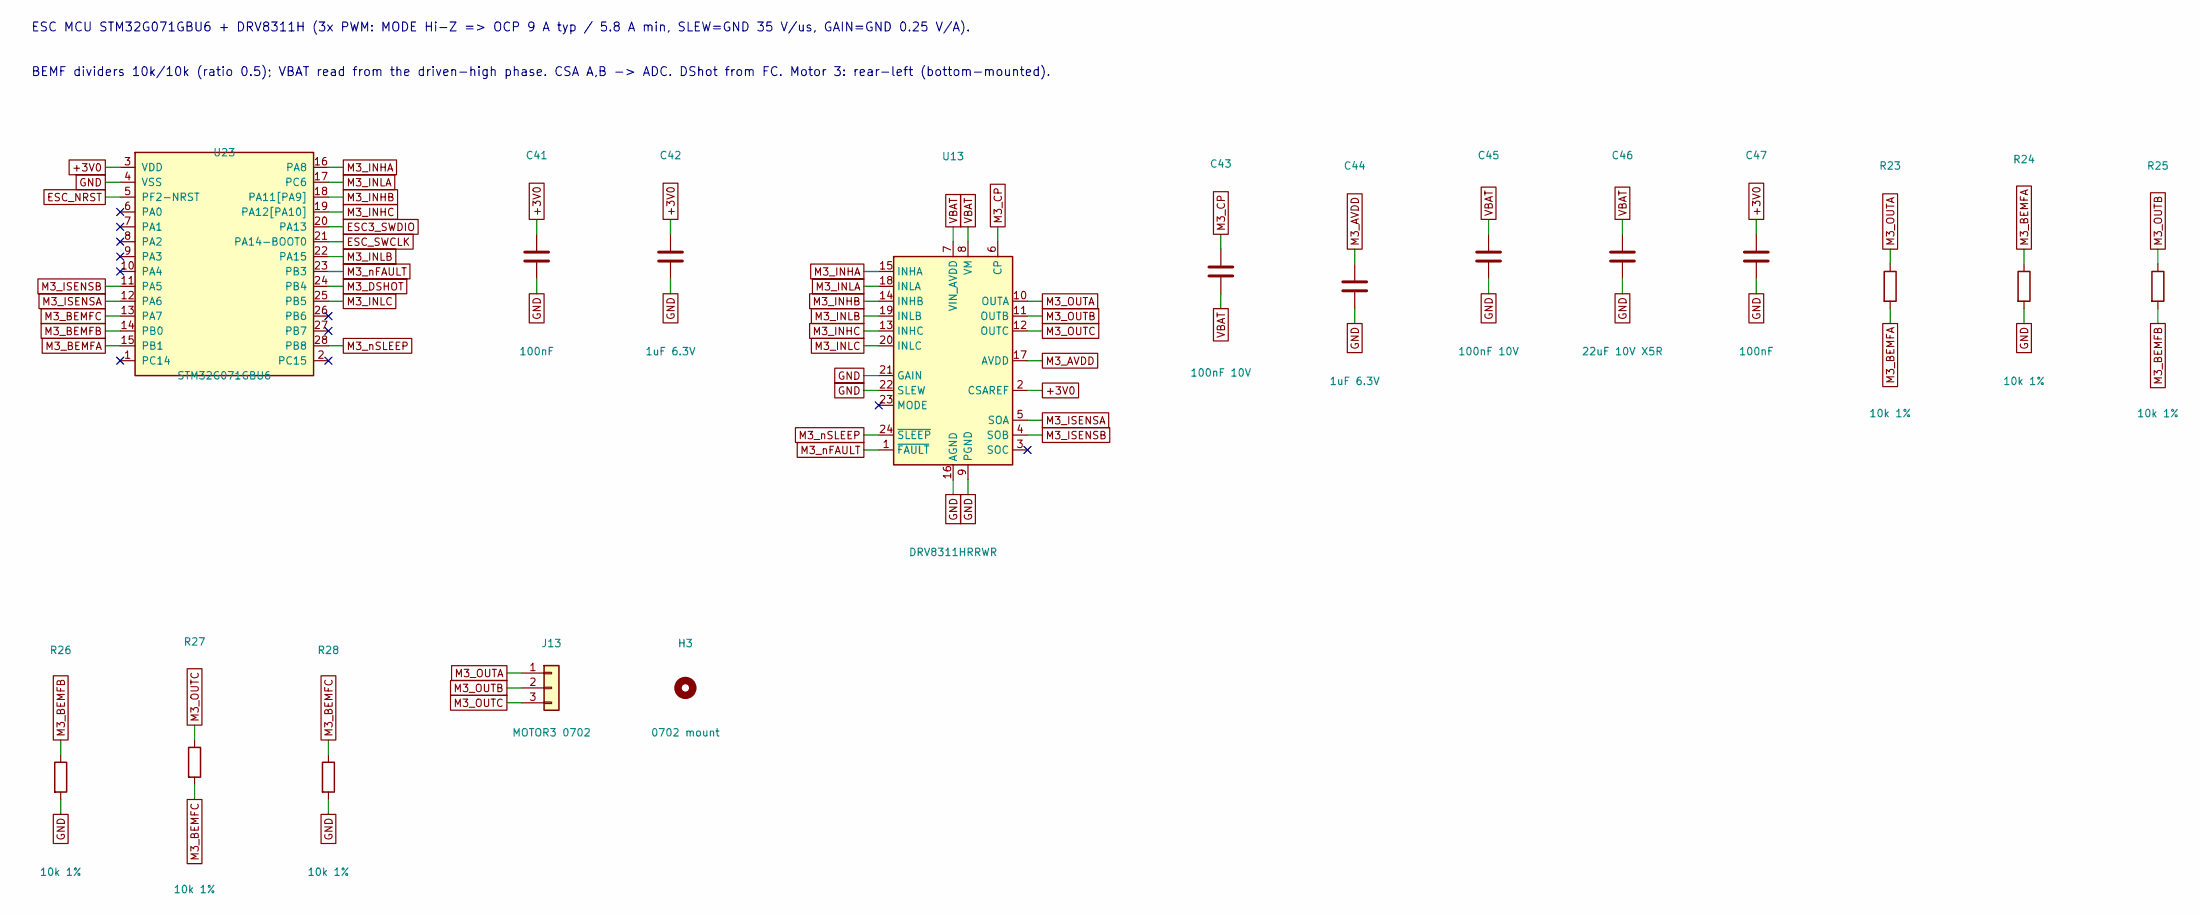
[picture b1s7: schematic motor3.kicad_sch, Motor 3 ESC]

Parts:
C41, C47: 100nF; C_0201_0603Metric
C42, C44: 1uF 6.3V; C_0201_0603Metric
C43, C45: 100nF 10V; C_0201_0603Metric
C46: 22uF 10V X5R; C_0603_1608Metric
H3: 0702 mount; Motor_0702_Mount
J13: MOTOR3 0702; MotorPads_3x_PTH
R23, R24, R25, R26, R27, R28: 10k 1%; R_0201_0603Metric
U13: DRV8311HRRWR; Texas_RRW0024A_WQFN-24-1EP_3x3mm_P0.4mm_EP1.9x1.9mm_Thermal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; MPN DRV8311HRRWR; LCSC C5218862
U23: STM32G071GBU6; QFN-28_4x4mm_P0.5mm; MPN STM32G071GBU6; LCSC C529347

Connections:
+3V0: C41.1, C42.1, C47.1, U13.2 (CSAREF), U23.3 (VDD); also elsewhere on the board
ESC3_SWDIO: U23.20 (PA13); also elsewhere on the board
ESC_NRST: U23.5 (PF2-NRST); also elsewhere on the board
ESC_SWCLK: U23.21 (PA14-BOOT0); also elsewhere on the board
GND: C41.2, C42.2, C44.2, C45.2, C46.2, C47.2, R24.2, R26.2, R28.2, U13.9 (PGND), U13.16 (AGND), U13.21 (GAIN), U13.22 (SLEW), U13.25 (PGND), U23.4 (VSS); also elsewhere on the board
M3_AVDD: C44.1, U13.17 (AVDD)
M3_BEMFA: R23.2, R24.1, U23.15 (PB1)
M3_BEMFB: R25.2, R26.1, U23.14 (PB0)
M3_BEMFC: R27.2, R28.1, U23.13 (PA7)
M3_CP: C43.1, U13.6 (CP)
M3_DSHOT: U23.24 (PB4); also elsewhere on the board
M3_INHA: U13.15 (INHA), U23.16 (PA8)
M3_INHB: U13.14 (INHB), U23.18 (PA11[PA9])
M3_INHC: U13.13 (INHC), U23.19 (PA12[PA10])
M3_INLA: U13.18 (INLA), U23.17 (PC6)
M3_INLB: U13.19 (INLB), U23.22 (PA15)
M3_INLC: U13.20 (INLC), U23.25 (PB5)
M3_ISENSA: U13.5 (SOA), U23.12 (PA6)
M3_ISENSB: U13.4 (SOB), U23.11 (PA5)
M3_OUTA: J13.1, R23.1, U13.10 (OUTA)
M3_OUTB: J13.2, R25.1, U13.11 (OUTB)
M3_OUTC: J13.3, R27.1, U13.12 (OUTC)
M3_nFAULT: U13.1 (~FAULT), U23.23 (PB3)
M3_nSLEEP: U13.24 (~SLEEP), U23.28 (PB8)
VBAT: C43.2, C45.1, C46.1, U13.7 (VIN_AVDD), U13.8 (VM); also elsewhere on the board

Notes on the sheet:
ESC MCU STM32G071GBU6 + DRV8311H (3x PWM: MODE Hi-Z => OCP 9 A typ / 5.8 A min, SLEW=GND 35 V/us, GAIN=GND 0.25 V/A).
BEMF dividers 10k/10k (ratio 0.5); VBAT read from the driven-high phase. CSA A,B -> ADC. DShot from FC. Motor 3: rear-left (bottom-mounted).
